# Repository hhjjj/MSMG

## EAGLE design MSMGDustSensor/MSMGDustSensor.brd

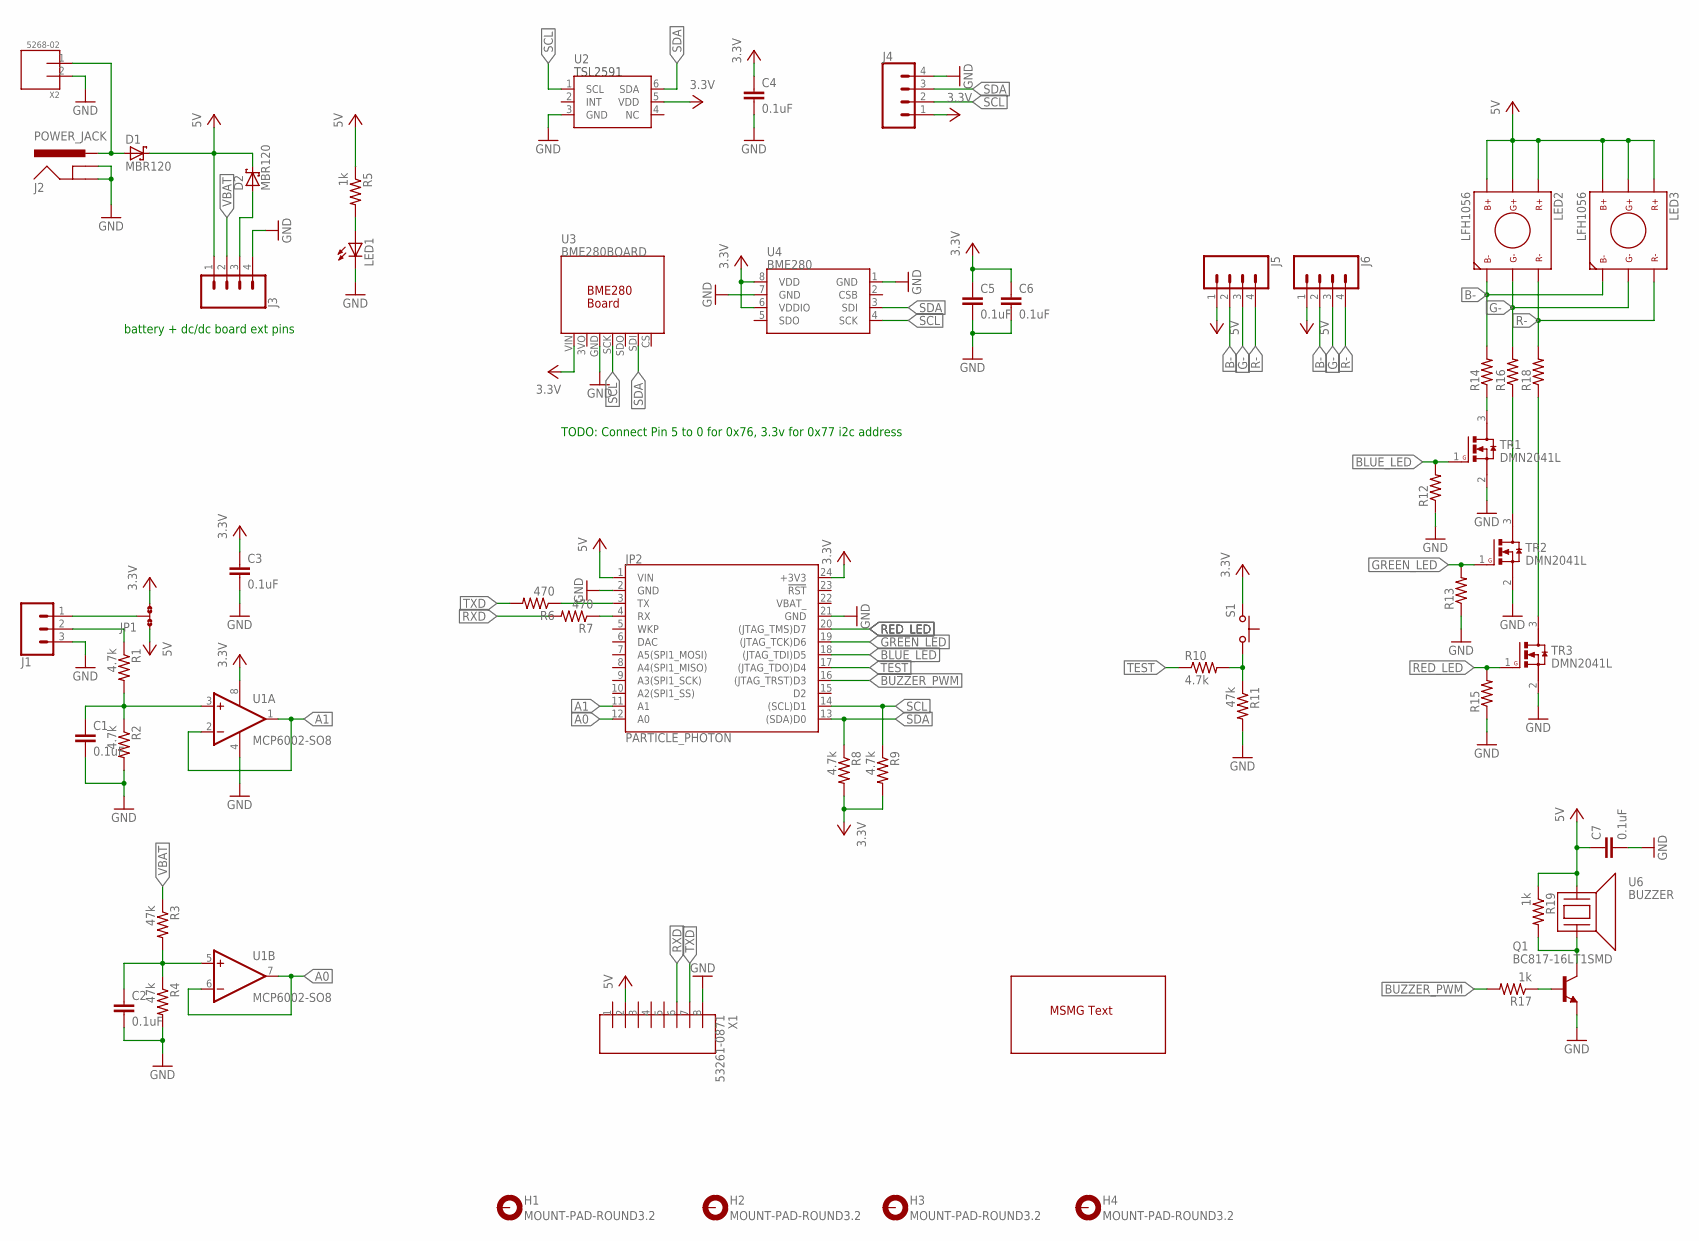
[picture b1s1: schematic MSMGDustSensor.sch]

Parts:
C1, C2, C3, C4, C5, C6, C7: 0.1uF; C0603(1608)
D1, D2: MBR120; SOD-123
H1, H2, H3, H4: MOUNT-PAD-ROUND3.2; 3,2-PAD
J1: CONN_03; 1X03
J2: POWER_JACK; POWER_JACK_PTH
J3, J4, J5, J6: CONN_04; 1X04
JP1: JP2; JP2SMD0603
JP2: PARTICLE_PHOTON
LED1: LED3MM
LED2, LED3: LFH1056
Q1: BC817-16LT1SMD; SOT23-BEC
R1, R2, R8, R9, R10: 4.7k; R0603(1608)
R3, R4, R11: 47k; R0603(1608)
R5, R17, R19: 1k; R0603(1608)
R6, R7: 470; R0603(1608)
R12, R13, R14, R15, R16, R18: R0603(1608)
S1: SWITCH; SKHLACA010
TR1, TR2, TR3: DMN2041L; SOT23
U1: MCP6002-SO8; SO8
U2: TSL2591; DFN-6
U3: BME280BOARD
U4: BME280
U6: BUZZER; PS1240
U$1: MSMG_TEXT
X1: 53261-0871
X2: 5268-02; 5628-02

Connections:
3.3V: C3.1, C4.1, C5.1, C6.1, J4.1, JP1.3, JP2.24 (+3V3), R8.2, R9.2, S1.P$1, U1.8 (V+), U2.5 (VDD), U3.VIN, U4.6 (VDDIO), U4.8 (VDD)
5V: C7.1, D1.C, D2.C, J3.1, J5.1, J6.1, JP1.1, JP2.1 (VIN), LED2.B+, LED2.G+, LED2.R+, LED3.B+, LED3.G+, LED3.R+, R5.1, R19.1, U6.1, X1.2
A0: JP2.12 (A0), U1.6 (-IN), U1.7 (OUT)
A1: JP2.11 (A1), U1.1 (OUT), U1.2 (-IN)
B-: J5.2, J6.2, LED2.B-, LED3.B-, R14.2
BLUE_LED: JP2.18 ((JTAG_TDI)D5), R12.2, TR1.1 (G)
BUZZER_PWM: JP2.16 ((JTAG_TRST)D3), R17.2
G-: J5.3, J6.3, LED2.G-, LED3.G-, R16.2
GND: C1.2, C2.2, C3.2, C4.2, C5.2, C6.2, C7.2, J1.3, J2.GND, J2.GNDBREAK, J3.4, J4.4, JP2.2 (GND), JP2.21 (GND), LED1.K (C), Q1.E, R2.2, R4.2, R11.2, R12.1, R13.1, R15.1, TR1.2 (S), TR2.2 (S), TR3.2 (S), U1.4 (V-), U2.3 (GND), U3.GND, U4.1 (GND), U4.7 (GND), X1.8, X2.2
GREEN_LED: JP2.19 ((JTAG_TCK)D6), R13.2, TR2.1 (G)
unnamed: D1.A, J2.PWR, X2.1
unnamed: D2.A, J3.3
unnamed: J1.2, R1.1
unnamed: JP2.3 (TX), R6.1
unnamed: J1.1, JP1.2
unnamed: JP2.4 (RX), R7.1
unnamed: R14.1, TR1.3 (D)
unnamed: R10.2, R11.1, S1.P$2
unnamed: R16.1, TR2.3 (D)
unnamed: Q1.C, R19.2, U6.2
unnamed: C2.1, R3.2, R4.1, U1.5 (+IN)
unnamed: R18.1, TR3.3 (D)
unnamed: C1.1, R1.2, R2.1, U1.3 (+IN)
unnamed: LED1.A, R5.2
unnamed: Q1.B, R17.1
R-: J5.4, J6.4, LED2.R-, LED3.R-, R18.2
RED_LED: JP2.20 ((JTAG_TMS)D7), R15.2, TR3.1 (G)
RXD: R7.2, X1.6
SCL: J4.2, JP2.14 ((SCL)D1), R9.1, U2.1 (SCL), U3.SCK, U4.4 (SCK)
SDA: J4.3, JP2.13 ((SDA)D0), R8.1, U2.6 (SDA), U3.SDI, U4.3 (SDI)
TEST: JP2.17 ((JTAG_TDO)D4), R10.1
TXD: R6.2, X1.7
VBAT: J3.2, R3.1
VBAT_: JP2.22 (VBAT_)

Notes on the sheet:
battery + dc/dc board ext pins
TODO: Connect Pin 5 to 0 for 0x76, 3.3v for 0x77 i2c address

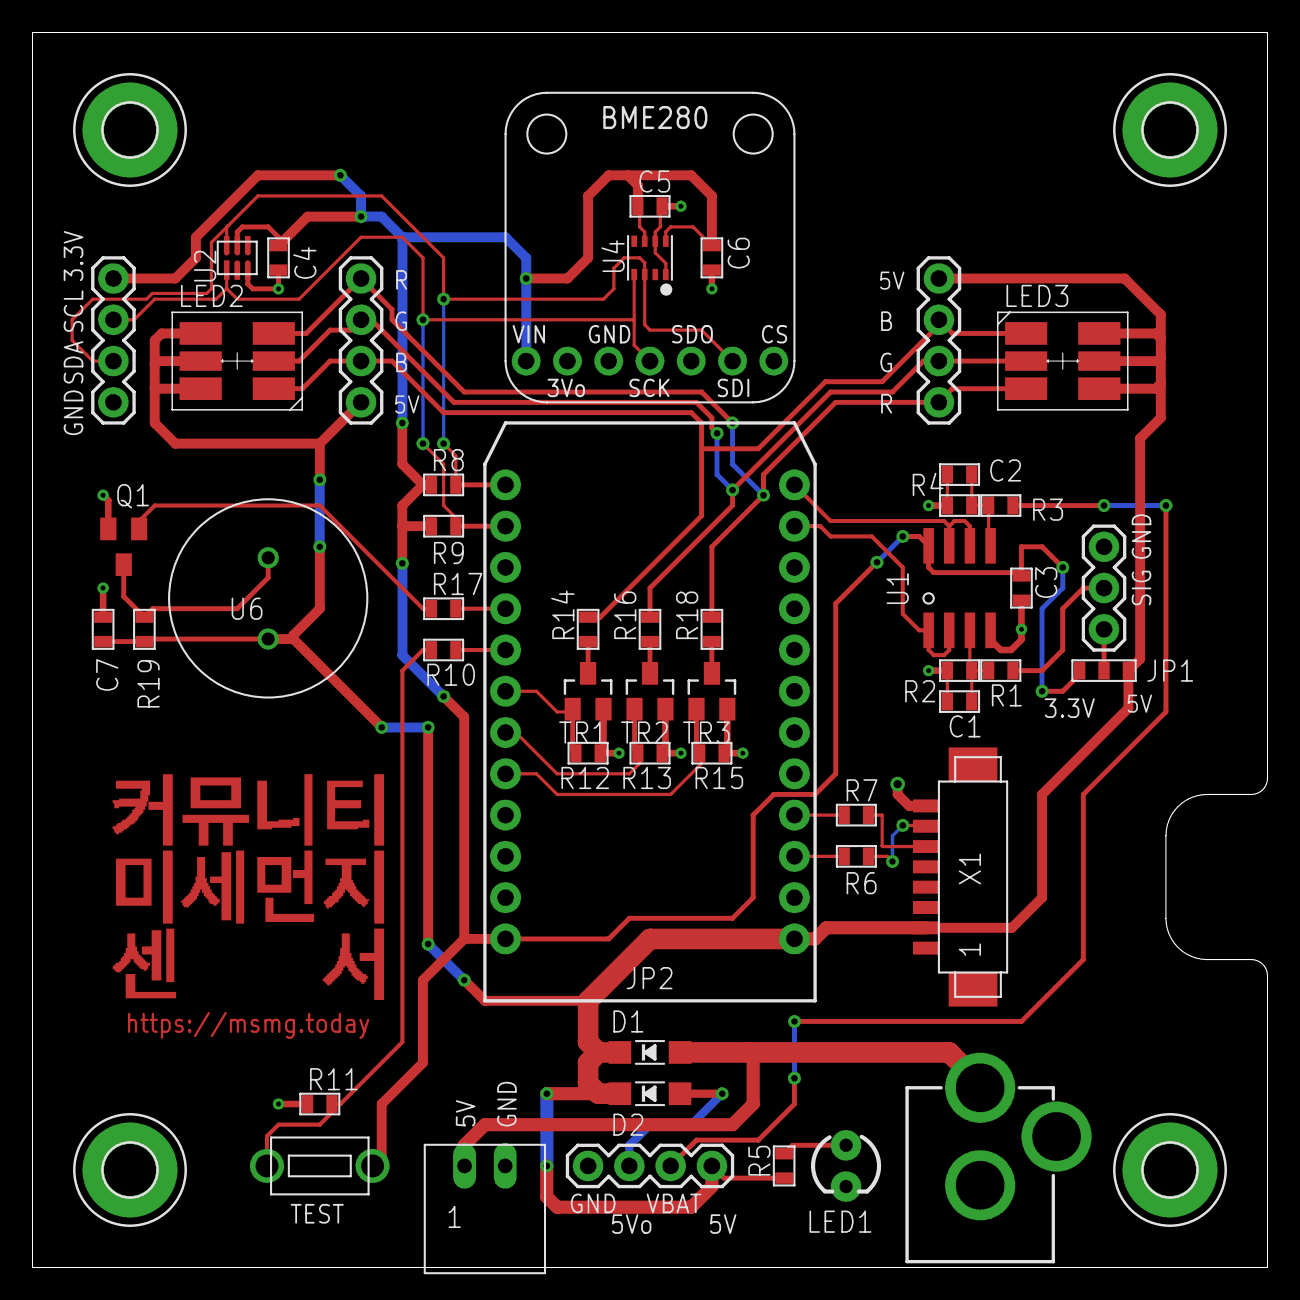
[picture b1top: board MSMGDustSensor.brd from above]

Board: 2 copper layers, 76.0 x 76.0 mm, 56 parts (0 on the bottom side), 33 nets.

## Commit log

2017-08-06 first
2017-08-06 lbr created
2017-08-06 dust sensor
2017-08-13 schematic almost done
2017-08-14 schematic clean up
2017-08-16 board file almost done
2017-08-16 almost done
2017-08-16 gerber done
2017-08-22 minor
2017-08-28 TODO added

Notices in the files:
parts and their libraries:
SparkFun-Connectors: Licensing: Creative Commons ShareAlike 4.0 International - https://creativecommons.org/licenses/by-sa/4.0
